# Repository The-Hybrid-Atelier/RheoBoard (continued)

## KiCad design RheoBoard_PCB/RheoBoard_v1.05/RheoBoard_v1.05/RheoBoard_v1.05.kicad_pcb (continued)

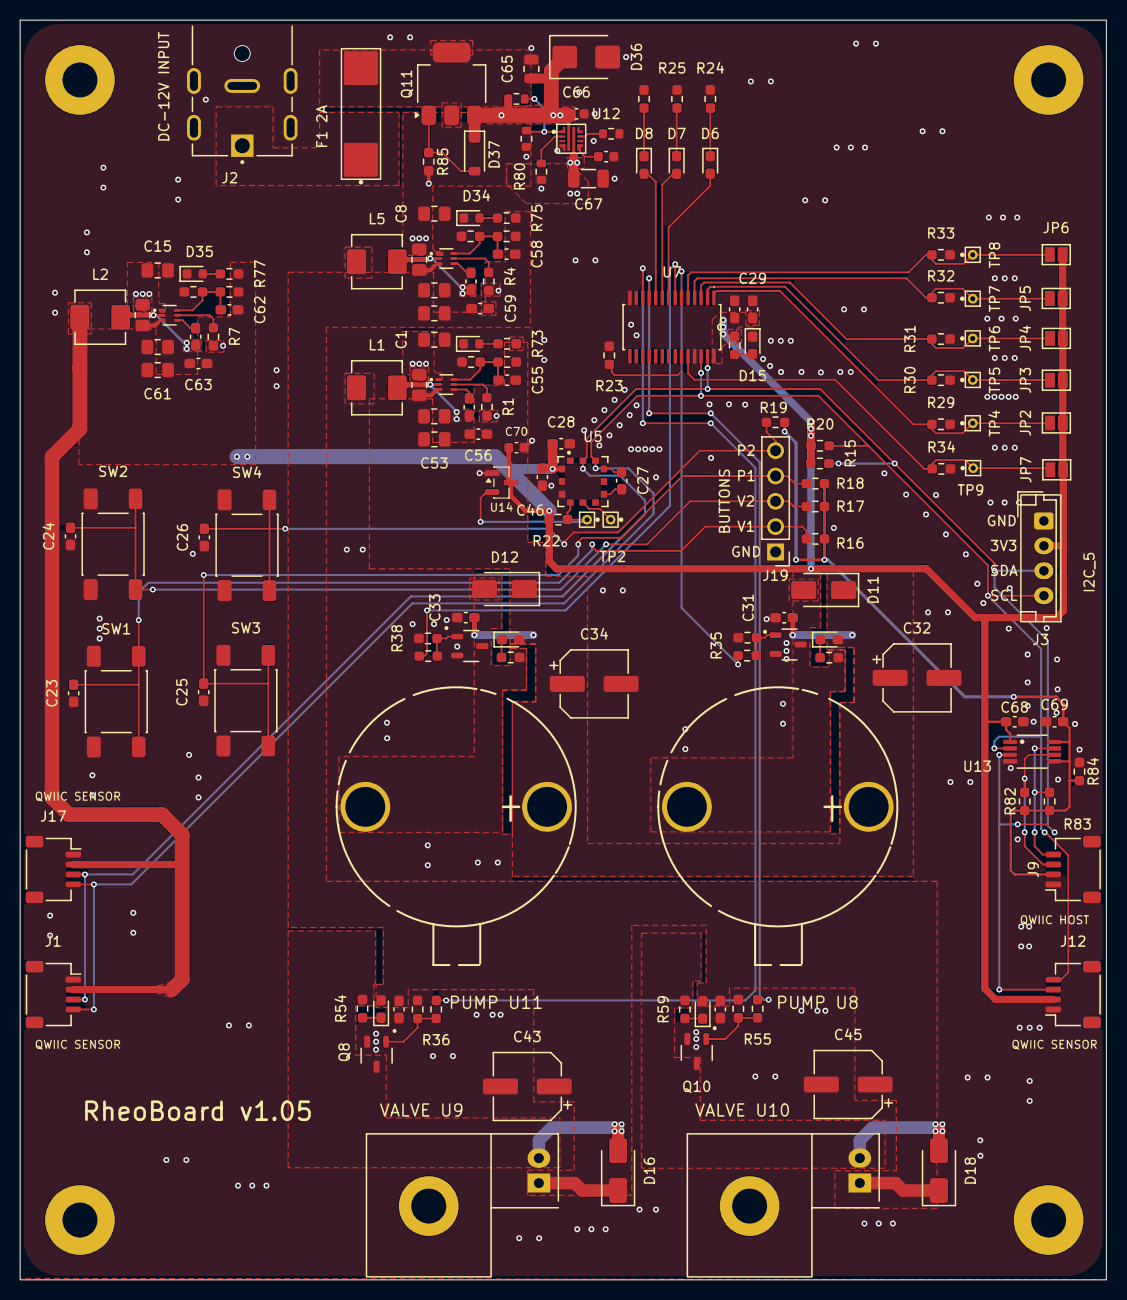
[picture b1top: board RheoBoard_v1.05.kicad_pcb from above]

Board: 2 copper layers, 109.0 x 126.4 mm, 162 parts (0 on the bottom side), 71 nets.

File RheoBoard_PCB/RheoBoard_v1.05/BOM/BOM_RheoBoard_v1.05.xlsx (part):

Comment | Designator | Footprint | LCSC / JLCPCB part | Qty | Unit USD (5-board order) | Fitted parts / board USD | Selected part source | Datasheet / specification | Manufacturer part number | Manufacturer | Assembly | Revision notes | Maximum allowed tolerance | Substitution requirements | JLCPCB category | Available order quantity
10uF 25V X5R ±10% | C1, C2, C8, C9, C15, C16 | Capacitor_SMD:C_0805_2012Metric_Pad1.18x1.45mm_HandSolder | C5448891 | 6 | 0.0379 | 0.22740000000000002 | https://jlcpcb.com/partdetail/component/C5448891 |  | TCC0805X5R106K250FT | CCTC | SMT |  | 0.1 | Same capacitance, footprint, voltage and dielectric. Preserve effective capacit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 | Extended | 149131
100nF 50V X7R ±10% | C3, C4, C5, C23, C24, C25, C26, C30, C31, C33, C42, C44, C46, C56, C59, C63, C6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 | Capacitor_SMD:C_0603_1608Metric_Pad1.08x0.95mm_HandSolder | C14663 | 18 | 0.0081 | 0.14579999999999999 | https://jlcpcb.com/partdetail/component/C14663 |  | CC0603KRX7R9BB104 | YAGEO | SMT | C68/C69 added as local/host U13 supply bypass. | 0.1 | Same capacitance, footprint, voltage and dielectric. Preserve effective capacit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 | Basic | 30393077
1nF 50V X7R ±5% | C27 | Capacitor_SMD:C_0603_1608Metric_Pad1.08x0.95mm_HandSolder | C5360811 | 1 | 0.0050999999999999995 | 0.0050999999999999995 | https://jlcpcb.com/partdetail/component/C5360811 |  | TCC0603X7R102J500CT | CCTC | SMT |  | 0.05 | Same capacitance, footprint, voltage and dielectric. Preserve effective capacit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 | Extended | 71799
10uF 25V X5R ±10% | C28, C29 | Capacitor_SMD:C_0603_1608Metric_Pad1.08x0.95mm_HandSolder | C7393892 | 2 | 0.0356 | 0.0712 | https://jlcpcb.com/partdetail/component/C7393892 |  | TCC0603X5R106K250CT | CCTC | SMT |  | 0.1 | Same capacitance, footprint, voltage and dielectric. Preserve effective capacit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 | Extended | 402730
22uF 50V ±20% | C32, C34, C43, C45 | Capacitor_SMD:CP_Elec_6.3x5.8 | C128458 | 4 | 0.179 | 0.716 | https://jlcpcb.com/partdetail/component/C128458 | https://industrial.panasonic.com/cdbs/www-data/pdf/RDE0000/A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 | EEEFK1H220P | Panasonic | SMT | Reduced from 100uF to 22uF; each pump/valve rail is approximately 88.3uF nomina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 | 0.2 | Same capacitance, footprint, voltage and dielectric. Preserve effective capacit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 | Extended | 5494
22uF 25V X5R ±20% | C52, C53, C54, C57, C60, C61 | Capacitor_SMD:C_0805_2012Metric_Pad1.18x1.45mm_HandSolder | C20416420 | 6 | 0.1334 | 0.8004 | https://jlcpcb.com/partdetail/component/C20416420 |  | TCC0805X5R226M250FT | CCTC | SMT |  | 0.2 | Same capacitance, footprint, voltage and dielectric. Preserve effective capacit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 | Extended | 87761
18pF 50V C0G ±5% | C55 | Capacitor_SMD:C_0603_1608Metric_Pad1.08x0.95mm_HandSolder | C107040 | 1 | 0.0067 | 0.0067 | https://jlcpcb.com/partdetail/component/C107040 |  | CC0603JRNPO9BN180 | YAGEO | SMT | 18 pF C0G 5%; same nominal value. | 0.05 | 5% or better, 18 pF C0G/NP0, >=50 V, 0603. Do not use X7R/X5R here. | Extended | 697605
24pF 50V C0G ±5% | C62 | Capacitor_SMD:C_0603_1608Metric_Pad1.08x0.95mm_HandSolder | C107044 | 1 | 0.0109 | 0.0109 | https://jlcpcb.com/partdetail/component/C107044 |  | CC0603JRNPO9BN240 | YAGEO | SMT | 24 pF C0G 5%; scales feed-forward timing for R61 100k. Bench transient check re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 | 0.05 | 5% or better, 24 pF C0G/NP0, >=50 V, 0603. | Extended | 23936
3.3nF 50V X7R ±10% | C64 | Capacitor_SMD:C_0603_1608Metric | C107088 | 1 | 0.0055 | 0.0055 | https://jlcpcb.com/partdetail/component/C107088 |  | CC0603KRX7R9BB332 | YAGEO | SMT | New controlled-startup timing capacitor for U12. | 0.1 | Same capacitance, footprint, voltage and dielectric. Preserve effective capacit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 | Extended | 506819
1uF 50V X7R ±10% | C65 | Capacitor_SMD:C_0805_2012Metric | C91185 | 1 | 0.0348 | 0.0348 | https://jlcpcb.com/partdetail/component/C91185 | https://www.yageogroup.com/download/specsheet/CC0805KKX7R9BB105 | CC0805KKX7R9BB105 | YAGEO | SMT | New local input bypass for U12; place beside IN/GND. | 0.1 | Same capacitance, footprint, voltage and dielectric. Preserve effective capacit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 | Extended | 317889
100nF 50V X7R ±10% | C66, C70 | Capacitor_SMD:C_0603_1608Metric | C14663 | 2 | 0.0081 | 0.0162 | https://jlcpcb.com/partdetail/component/C14663 |  | CC0603KRX7R9BB104 | YAGEO | SMT | Local high-frequency bypass for U12 and U14. | 0.1 | Same capacitance, footprint, voltage and dielectric. Preserve effective capacit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 | Basic | 30393077
4.7uF 50V X7R ±10% | C67 | Capacitor_SMD:C_1206_3216Metric | C132170 | 1 | 0.1189 | 0.1189 | https://jlcpcb.com/partdetail/component/C132170 | https://www.yageogroup.com/download/specsheet/CC1206KKX7R9BB475 | CC1206KKX7R9BB475 | YAGEO | SMT | New local output bypass for U12; place beside OUT/GND. | 0.1 | Same capacitance, footprint, voltage and dielectric. Preserve effective capacit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 | Extended | 16653
DMP6023LE-13 | Q11 | RheoBoard:SOT-223-3_TabPin2_DFM | C154901 | 1 | 0.624 | 0.624 | https://jlcpcb.com/partdetail/component/C154901 | https://www.diodes.com/datasheet/download/DMP6023LE.pdf | DMP6023LE-13 | Diodes Incorporated | SMT | Replaces D1 with lower-loss reverse-polarity protection. 1 gate, 2 drain/tab to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 |  |  | Extended | 476
LED_Red | D6, D7, D8, D13, D14, D15, D17, D19 | RheoBoard:LED_SZYY0603R_A1_K2_HandSolder | C434419 | 8 | 0.0137 | 0.1096 | https://jlcpcb.com/partdetail/component/C434419 | https://datasheet.lcsc.com/datasheet/pdf/7948f9a4498910c84f6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 | SZYY0603R | Yongyu Photoelectric | SMT | Manufacturer numbering: 1=A(+), 2=K(-). Cathode bar marks pad 2. See LED assemb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 |  |  | Extended | 830337
SS34 | D11, D12, D16, D18 | Diode_SMD:D_SMA | C115205 | 4 | 0.037700000000000004 | 0.15080000000000002 | https://jlcpcb.com/partdetail/component/C115205 |  | SS34 | Jingdao Microelectronics | SMT | SMA footprint and polarity mark match selected Jingdao SS34. |  |  | Extended | 61565
LED_Red | D33, D34, D35 | RheoBoard:LED_SZYY0603R_A1_K2_Nominal | C434419 | 3 | 0.0137 | 0.0411 | https://jlcpcb.com/partdetail/component/C434419 | https://datasheet.lcsc.com/datasheet/pdf/7948f9a4498910c84f6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 | SZYY0603R | Yongyu Photoelectric | SMT | Manufacturer numbering: 1=A(+), 2=K(-). Cathode bar marks pad 2. See LED assemb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 |  |  | Extended | 830337
SMBJ13A | D36 | Diode_SMD:D_SMB | C151252 | 1 | 0.14250000000000002 | 0.14250000000000002 | https://jlcpcb.com/partdetail/component/C151252 | https://www.littelfuse.com/assetdocs/tvs-diodes-smbj-series-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 | SMBJ13A | Littelfuse | SMT | Exact Littelfuse SMBJ13A. 13 V standoff, 21.5 V clamp at 28 A. Marking LG; cath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 |  |  | Extended | 1226
2A time-delay JFC1032-1200TS | F1 | RheoBoard:Fuse_JDT_JFC1032TS_10.25x3.2mm | C53035082 | 1 | 0.2938 | 0.2938 | https://jlcpcb.com/partdetail/component/C53035082 | https://www.jdtfuse.com/upload/PDF/JFC1032TS.pdf | JFC1032-1200TS | JDTfuse | SMT | Corrected centered origin and JDT land pattern. Check the new placement preview. |  |  | Extended | 1504
JST SH 4-pin 1.00mm | J1, J9, J12, J17 | Connector_JST:JST_SH_SM04B-SRSS-TB_1x04-1MP_P1.00mm_Horizontal | C160404 | 4 | 0.2149 | 0.8596 | https://jlcpcb.com/partdetail/component/C160404 | https://www.jst-mfg.com/product/pdf/eng/eSH.pdf | SM04B-SRSS-TB(LF)(SN) | JST | SMT | Standard Qwiic pin order: 1 GND, 2 3.3 V, 3 SDA, 4 SCL. J9 is the dedicated MAS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 |  |  | Extended | 65620
PJ-082BH | J2 | RheoBoard:PJ-082BH | C3094233 | 1 | 2.608 | 2.608 | https://www.lcsc.com/product-detail/C3094233.html | https://www.sameskydevices.com/product/resource/pj-082bh.pdf | PJ-082BH | CUI | Manual THT | Manual through-hole assembly. Center-positive 12 V, 5.5 x 2.5 mm mating plug.
JST EH 4-pin 2.50mm | J3 | RheoBoard:JST_EH_B4B-EH-A_1x04_P2.50mm_Vertical_DFM | C160258 | 1 | 0.0613 | 0.0613 | https://www.lcsc.com/product-detail/C160258.html | https://www.jst-mfg.com/product/pdf/eng/eEH.pdf | B4B-EH-A(LF)(SN) | JST | Manual THT | Manual through-hole assembly. Pin 2 supplies local 3.3 V to peripherals.
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
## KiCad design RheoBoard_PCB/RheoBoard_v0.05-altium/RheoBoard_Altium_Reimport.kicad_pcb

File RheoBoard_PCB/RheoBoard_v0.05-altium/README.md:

# RheoBoard v0.05 Altium conversion

Open `RheoBoard_Altium_Reimport.kicad_pro` in KiCad 10. This historical conversion is separate from the later native v1 and v1.05 designs. The original Altium archive is retained in `RheoBoard_v0.05.rar`.

The import recovered MAIN, POWER and a drawing-only block-diagram sheet, plus a two-layer PCB and its imported footprint library. Eight external illustrations were unavailable. The flat schematic sheets require connectivity and reference reconciliation before schematic-to-board updates.

This conversion is not ready for fabrication. The retained design includes a backside copper overlap between pump 1 and a valve switched node, an unconnected controller LED5 output and missing valve-2 controller drive, plus ERC/DRC findings involving clearances, copper edges, annular rings, mask and imported library links. No fabrication package was regenerated for this conversion. Use the later revision folders for their corresponding designs; do not mix their outputs.

Hardware design licensing follows the repository root LICENSE, CERN-OHL-W-2.0. Documentation is CC BY-SA 4.0.

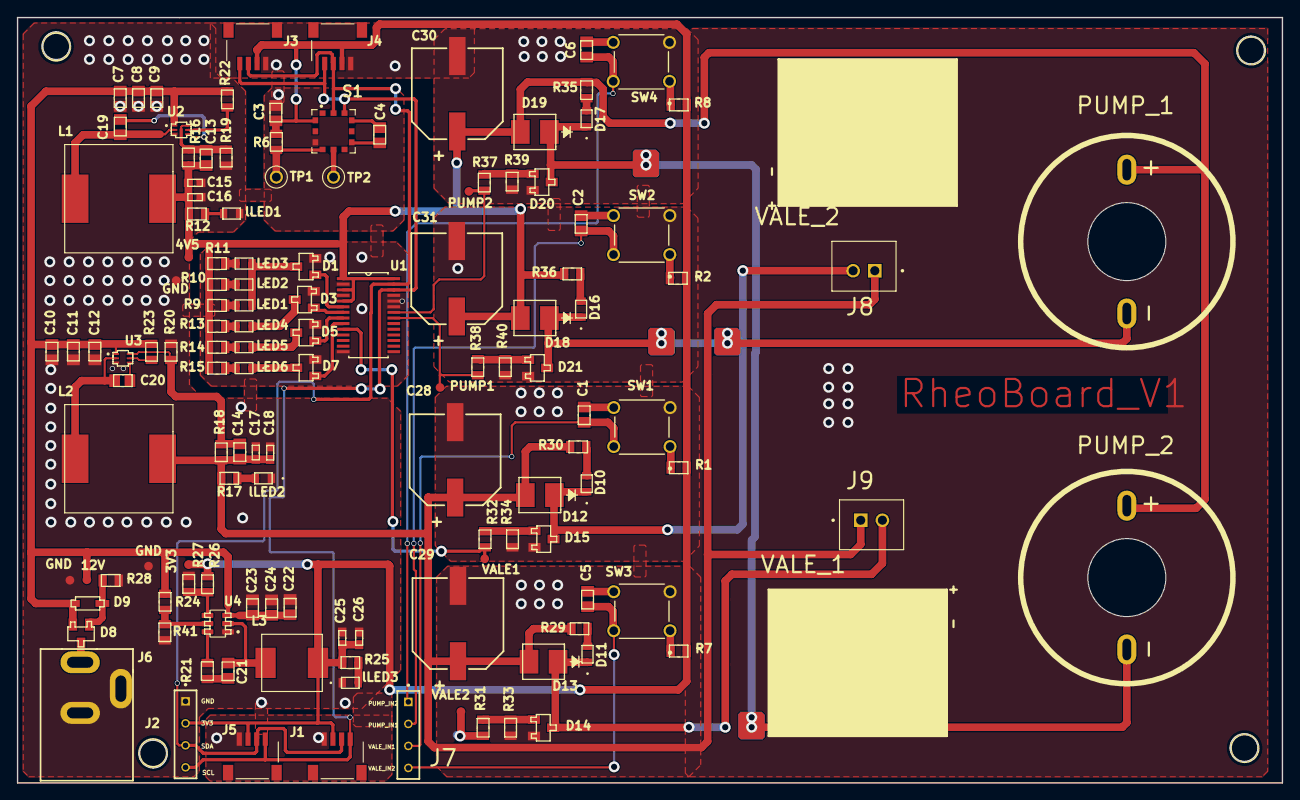
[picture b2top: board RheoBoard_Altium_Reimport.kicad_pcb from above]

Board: 2 copper layers, 146.0 x 88.3 mm, 132 parts (0 on the bottom side), 71 nets.

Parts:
3V3, 4V5, 12V: TP_1MM; TP_1mm
C1, C2, C3, C5, C6, C9, C12, C19, C20, C21, C22: 0.1UF,50V; CAP_CER_0805
C4: 1nF 50V; CAP_CER_0805
C7, C8, C10, C11: 10UF 50V; CAP_CER_0805
C13, C14: 18pF 50V; CAP_CER_0805
C15, C16, C17, C18, C25, C26: 22uF 6.3V; CAP_CER_0603
C23, C24: 10UF 25V; CAP_CER_0805
C28, C29, C30, C31: 100uF 25V; CAP_ALUM_SMD_D10_H12.4
D1, D3, D5, D7, D14, D15, D20, D21: 30V 5.8A; SOT-23-3
D8: 20V 4A; SOT-23-3
D9: BZT52C5V1; SOD-123
D10, D11, D16, D17: Led green; LED_LS R976_AOS
D12, D13, D18, D19: 3A 40V; DO214AA
GND: TP_1MM; TP_1mm
GND#2, GND#3: TP_1MM; TP_1mm
J1, J3, J4, J5: 14417; SPARKFUN_PRT-14417
J2: TS-104-T-A; HDR_THT_1X04_P2.54
J6: 694106301002; CONN PWR JACK 2.1X5.5MM SOLDER
J7: TS-104-T-A; HDR_THT_1x04_P2.54
J8, J9: VERT; CONN_SMD_TOP_P2.50
L1, L2: 2.2uH; IND_12.5x12.5_H8.5
L3: 4.7uH; IND_6.8X6.5_H2.8
LED1, LED2, LED3: RED 2V 20mA; LED_LS R976_AOS
LED4, LED5, LED6: Led green; LED_LS R976_AOS
PUMP1, PUMP2: TP_1MM; TP_1mm
PUMP_1, PUMP_2: 0010844022; PUMP_LPM - ZR370-02PM
R1, R2, R6, R7, R8, R33, R34, R39, R40: 10K 1% 0805; RES_0805
R9, R10, R11, R13, R14, R15, R29, R30, R35, R36: 220R 0805; RES_0805
R12, R17: 1K 1% 0805; RES_0805
R16: 130K 0805; RES_0805
R18: 270K 0805; RES_0805
R19: 20K 0805; RES_0805
R20: 30K 0805; RES_0805
R21: 30Ohm 0805; RES_0805
R22, R23, R28: 100K 0805; RES_0805
R24: 174K 0805; RES_0805
R25: 470R 0805; RES_0805
R26: 75K 0805; RES_0805
R27: 24K 0805; RES_0805
R31, R32, R37, R38: 100R 0805; RES_0805
R41: 36.5K 0805; RES_0805
S1: MPRLS0025PA00001A; XDCR_MPRLS0025PA00001A
SW1, SW2, SW3, SW4: B3F-1020; SW_B3F-1000_OMR
TP1, TP2: 5002; KEYSTONE_5002
U1: PCA9685PW,118; TSSOP-28
U2, U3: TPS563203DRLR; SOT-563
U4: TPS56339DDCT; SOT-23-6
VALE1, VALE2: TP_1MM; TP_1mm
VALE_1, VALE_2: 0010844022; VALE_FA0520E
lLED1, lLED2, lLED3: RED 2V 20mA; LED_LS R976_AOS

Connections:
+12: 12V.1, C7.2, C8.2, C9.2, C10.2, C11.2, C12.2, C22.2, C23.2, C24.2, D8.2, D9.1, R22.2, R23.2, R24.2, U2.1, U3.1, U4.3
GND: C3.2, C7.1, C8.1, C9.1, C10.1, C11.1, C12.1, C15.1, C16.1, C17.1, C18.1, C22.1, C23.1, C24.1, C25.1, C26.1, C28.2, C29.2, C30.2, C31.2, D1.2, D3.2, D5.2, D7.2, D14.2, D15.2, D20.2, D21.2, GND.1, GND#2.1, GND#3.1, J1.1, J2.01, J3.1, J4.1, J5.1, J6.2, J6.3, R19.2, R20.1, R27.1, R28.1, R33.1, R34.1, R39.1, R40.1, R41.1, S1.10, SW1.3, SW2.3, SW3.3, SW4.3, U1.2, U1.4, U1.14, U1.23, U1.24, U1.25, U2.3, U3.3, U4.1, lLED1.1, lLED2.1, lLED3.1
Net3V3_1: 3V3.1, C3.1, C25.2, C26.2, J1.2, J2.02, J3.2, J4.2, J5.2, L3.2, R1.2, R2.2, R6.2, R7.2, R8.2, R25.2, R26.2, S1.12
Net4V5_1: 4V5.1, C13.2, C15.2, C16.2, C30.1, C31.1, D18.2, D19.2, L1.1, PUMP_1.1, PUMP_2.1, R9.2, R10.2, R11.2, R12.2, R13.1, R14.1, R15.1, R16.2, R35.1, R36.1, U1.1, U1.3, U1.5, U1.28
NetC1_1: C1.1, SW1.4
NetC2_1: C2.1, SW2.4
NetC4_1: C4.1, S1.6
NetC4_2: C4.2, S1.4
NetC5_1: C5.1, SW3.4
NetC6_1: C6.1, SW4.4
NetC13_1: C13.1, R16.1, R19.1, U2.6
NetC14_1: C14.1, R18.1, R20.2, U3.6
NetC14_2: C14.2, C17.2, C18.2, C28.1, C29.1, D12.2, D13.2, J8.1, J9.1, L2.1, R17.2, R18.2, R29.1, R30.1
NetC19_1: C19.1, L1.2, U2.2
NetC19_2: C19.2, U2.4
NetC20_1: C20.1, L2.2, U3.2
NetC20_2: C20.2, U3.4
NetC21_1: C21.1, L3.1, U4.2
NetC21_2: C21.2, R21.2
NetD1_1: D1.1, U1.6
NetD1_3: D1.3, LED1.1, LED2.1, LED3.1
NetD3_1: D3.1, U1.7
NetD3_3: D3.3, LED4.1
NetD5_1: D5.1, U1.8
NetD5_3: D5.3, LED5.1
NetD7_1: D7.1, U1.9
NetD7_3: D7.3, LED6.1
NetD8_1: D8.1, D9.2, R28.2
NetD8_3: D8.3, J6.1
NetD10_1: D10.1, D12.1, D15.3, J8.2
NetD10_2: D10.2, R30.2
NetD11_1: D11.1, D13.1, D14.3, J9.2
NetD11_2: D11.2, R29.2
NetD14_1: D14.1, R31.2, R33.2
NetD15_1: D15.1, R32.2, R34.2
NetD16_1: D16.1, D18.1, D21.3, PUMP_1.2
NetD16_2: D16.2, R36.2
NetD17_1: D17.1, D19.1, D20.3, PUMP_2.2
NetD17_2: D17.2, R35.2
NetD20_1: D20.1, R37.2, R39.2
NetD21_1: D21.1, R38.2, R40.2
NetLED1_2: LED1.2, R9.1
NetLED2_2: LED2.2, R10.1
NetLED3_2: LED3.2, R11.1
NetLED4_2: LED4.2, R13.2
NetLED5_2: LED5.2, R14.2
NetLED6_2: LED6.2, R15.2
NetPUMP1_1: PUMP1.1, R38.1, U1.21
NetPUMP2_1: PUMP2.1, R37.1, U1.22
NetR1_1: R1.1, SW1.1
NetR2_1: R2.1, SW2.1
NetR6_1: R6.1, S1.9, TP1.TP
NetR7_1: R7.1, SW3.1
NetR8_1: R8.1, SW4.1
NetR21_1: R21.1, U4.6
NetR22_1: R22.1, U2.5
NetR23_1: R23.1, U3.5
NetR24_1: R24.1, R41.2, U4.5
NetR26_1: R26.1, R27.2, U4.4
NetR31_1: R31.1, VALE2.1
NetR32_1: R32.1, U1.10, VALE1.1
NetS1_8: S1.8, TP2.TP
NetlLED1_2: R12.1, lLED1.2
NetlLED2_2: R17.1, lLED2.2
NetlLED3_2: R25.1, lLED3.2
PUMP1_IN: C2.2, J7.02, SW2.2
PUMP2_IN: C6.2, J7.01, SW4.2
SCL: J1.4, J2.04, J3.4, J4.4, J5.4, S1.3, U1.26
SDA: J1.3, J2.03, J3.3, J4.3, J5.3, S1.2, U1.27
VALE1_IN: C1.2, J7.03, SW1.2
VALE2_IN: C5.2, J7.04, SW3.2

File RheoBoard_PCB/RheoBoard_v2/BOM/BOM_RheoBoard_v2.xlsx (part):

RheoBoard v2 purchasing BOM
Quantities are for one board. Parts cost controls the batch size and shows whic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
Enter USD quotes in column F. Filter v1.05 reuse for shared parts. Check select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
Component | Designators | Altium footprint | Supplier SKU | Qty / board | Unit USD | Parts / board USD | Purchase source | Datasheet / spec | Sourcing MPN / model | Manufacturer | Assembly | Selection | Design MPN / model | Purchasing note | Min. order | Order multiple | Price from qty | Qty needed | Order qty | Order USD | Supplier | LCSC / JLCPCB ID | Catalog relationship | Price basis | Price through qty | Tolerance | v1.05 reuse | v1.05 source | Alternate source
16-channel PWM controller | U1 | TSSOP-28 | C2678753 | 1 |  |  | Supplier listing | Specification | PCA9685PW,118 | NXP Semiconductors | SMT | Selected | PCA9685PW,118 |  | 1 | 1 | 1 | 5 | 5 |  | LCSC | C2678753 | Design MPN | Enter supplier quote |  |  | Same MPN · C2678753 | v1.05 supplier
25 psi absolute I²C pressure sensor | S1 | XDCR_MPRLS0025PA00001A | C3257154 | 1 |  |  | Supplier listing | Specification | MPRLS0025PA00001A | Honeywell | SMT | Selected | MPRLS0025PA00001A |  | 1 | 1 | 1 | 5 | 5 |  | LCSC | C3257154 | Design MPN | Enter supplier quote |  |  | Same MPN · C3257154 | v1.05 supplier
3 A step-down regulator (4.5 V and 6 V rails) | U2, U3 | SOT-563 | 296-TPS563203DRLRCT-ND | 2 |  |  | Supplier listing | Specification | TPS563203DRLR | Texas Instruments | SMT | Selected | TPS563203DRLR |  | 1 | 1 | 1 | 10 | 10 |  | DigiKey | C22445512 | Design MPN | Enter supplier quote |  |  | Same MPN · C22445512 | v1.05 supplier
3 A step-down regulator (3.3 V rail) | U4 | SOT-23-6 | 296-53564-1-ND | 1 |  |  | Supplier listing | Specification | TPS56339DDCT | Texas Instruments | SMT | Selected | TPS56339DDCT |  | 1 | 1 | 1 | 5 | 5 |  | DigiKey | C2071585 | Design MPN | Enter supplier quote
2.2 µH shielded power inductor | L1, L2 | IND_12.5x12.5_H8.5 | 3502182 | 2 |  |  | Candidate source | Specification | B82477G4222M000 | TDK | SMT | Review | IFSC1515AHER2R2M01 | The 4 mm schematic part cannot span the 7 mm copper gap. TDK matches the lands.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 | 1 | 1 | 1 | 10 |  |  | DigiKey |  |  | Enter supplier quote |  | 20% |  |  | Design MPN only
4.7 µH power inductor | L3 | IND_6.8X6.5_H2.8 | 308-2466-1-ND | 1 |  |  | Supplier listing | Specification | 0630CDMCCDS-4R7MC | Sumida | SMT | Selected | 0630CDMCCDS-4R7MC |  | 1 | 1 | 1 | 5 | 5 |  | DigiKey | C167294 | Design MPN | Enter supplier quote |  | 20%
P-channel MOSFET | D8 | SOT-23-3 | C96616 | 1 |  |  | Supplier listing |  | DMG3415U-7 | Diodes Inc. | SMT | Selected | DMG3415U-7 |  | 5 | 5 | 1 | 5 | 5 |  | LCSC | C96616 | Design MPN | Enter supplier quote
5.1 V Zener diode | D9 | SOD-123 | BZT52C5V1-FDICT-ND | 1 |  |  | Supplier listing |  | BZT52C5V1-7-F | Diodes Inc. | SMT | Selected | BZT52C5V1-7-F |  | 1 | 1 | 1 | 5 | 5 |  | DigiKey | C151588 | Design MPN | Enter supplier quote |  | 6%
N-channel MOSFET | D1, D3, D5, D7, D14, D15, D20, D21 | SOT-23-3 | C20917 | 8 |  |  | Supplier listing |  | AO3400A | Alpha & Omega | SMT | Selected | AO3400A |  | 5 | 5 | 1 | 40 | 40 |  | LCSC | C20917 | Design MPN | Enter supplier quote |  |  | Same MPN · C20917 | v1.05 supplier
3 A, 40 V Schottky flyback diode | D12, D13, D18, D19 | DO214AA | C85099 | 4 |  |  | Candidate source | Specification | B340B-13-F | Diodes Incorporated | SMT | Review | SS34 | The onsemi SMC body exceeds the SMB footprint. Confirm the SMB candidate’s sold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 | 1 | 1 | 1 | 20 |  |  | JLCPCB |  |  | Enter supplier quote |  |  |  |  | Design MPN only
Red indicator LED, 0805 | LED1, LED2, LED3, lLED1, lLED2, lLED3 | LED_LS R976_AOS | 475-LSR976-NR-1CT-ND | 6 |  |  | Supplier listing |  | LS R976-NR-1-0-20-R18 | ams OSRAM | SMT | Selected | LS R976-NR-1-0-20-R18 |  | 1 | 1 | 1 | 30 | 30 |  | DigiKey | C2899997 | Design MPN | Enter supplier quote
Green indicator LED, 0805 lands | D10, D11, D16, D17, LED4, LED5, LED6 | LED_LS R976_AOS | C5456999 | 7 |  |  | Candidate source | Specification | LG R971-KN-1 | ams OSRAM | SMT | Review | LTST-C190GKT | Lite-On is 0603 on 0805 lands. Verify the OSRAM candidate’s polarity, pad overl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 | 1 | 1 | 1 | 35 |  |  | JLCPCB |  |  | Enter supplier quote |  |  |  |  | Design MPN only
4-pin Qwiic connector | J1, J3, J4, J5 | SPARKFUN_PRT-14417 | 1568-14417-ND | 4 |  |  | Supplier listing |  | 14417 | SparkFun | SMT | Selected | 14417 |  | 1 | 1 | 1 | 20 | 20 |  | DigiKey | C2859067 | Design MPN | Enter supplier quote |  |  | JST housing-color variant · C160404 | v1.05 supplier
4-position vertical pin header, 2.54 mm | J2, J7 | HDR_THT_1X04_P2.54 | 612-TS-104-T-A-ND | 2 |  |  | Supplier listing | Specification | TS-104-T-A | Samtec | Through-hole | Selected | TS-104-T-A | Use the Samtec -A lead option. Its recommended hole is 0.635 mm, matching the v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 | 1 | 1 | 1 | 10 | 10 |  | DigiKey | C6886151 | Design MPN | Enter supplier quote
DC jack, 2.1 × 5.5 mm | J6 | CONN PWR JACK 2.1X5.5MM SOLDER | 732-5930-ND | 1 |  |  | Supplier listing | Specification | 694106301002 | Würth Elektronik | Through-hole | Selected | 694106301002 |  | 1 | 1 | 1 | 5 | 5 |  | DigiKey |  |  | Enter supplier quote
2-position XH valve header, 2.50 mm | J8, J9 | CONN_SMD_TOP_P2.50 | C158012 | 2 |  |  | Supplier listing | Specification | B2B-XH-A(LF)(SN) | JST | Through-hole | Selected | B2B-XH-A |  | 20 | 20 | 1 | 10 | 20 |  | LCSC | C158012 | XH family, check plated suffix | Enter supplier quote |  |  | Matching XH header · C158012 | v1.05 supplier
Momentary tactile switch | SW1, SW2, SW3, SW4 | SW_B3F-1000_OMR | SW402-ND | 4 |  |  | Supplier listing |  | B3F-1020 | Omron | Through-hole | Selected | B3F-1020 |  | 1 | 1 | 1 | 20 | 20 |  | DigiKey | C722171 | Design MPN | Enter supplier quote
White miniature test point | TP1, TP2 | KEYSTONE_5002 | C238123 | 2 |  |  | Supplier listing |  | 5002 | Keystone | Through-hole | Selected | 5002 |  | 5 | 5 | 1 | 10 | 10 |  | LCSC | C238123 | Design MPN | Enter supplier quote
100 nF, 50 V, 0805 | C1, C2, C3, C5, C6, C9, C12, C19, C20, C21, C22 | CAP_CER_0805 | 0805B104J500BD | 11 |  |  | Candidate source | Specification | 0805B104J500BD | NextGen Component | SMT | Review | 0805B104K500BD | Schematic symbol specifies ±5%. Its named K-grade part is ±10%. The J-grade alt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 | 1 | 1 | 1 | 55 |  |  | NextGen Component |  |  | Enter supplier quote |  |  |  |  | Design MPN (±10%)
1 nF, 50 V, 0805 | C4 | CAP_CER_0805 | 399-C0805C102K5HACAUTOCT-ND | 1 |  |  | Supplier listing |  | C0805C102K5HACAUTO | Yageo Group | SMT | Selected | C0805C102K5HACAUTO |  | 1 | 1 | 1 | 5 | 5 |  | DigiKey | C1513171 | Design MPN | Enter supplier quote
10 µF, 50 V, 0805 | C7, C8, C10, C11 | CAP_CER_0805 | 3372-0805W106K500CCTR-ND | 4 |  |  | Supplier listing |  | 0805W106K500CC | Nextgen | SMT | Selected | 0805W106K500CC | The recorded NextGen/Aillen part is supplied in reels of 3,000. Samsung CL21A10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 | 3000 | 3000 | 1 | 20 | 3000 |  | DigiKey Marketplace |  |  | Enter supplier quote |  |  |  |  | Samsung candidate
18 pF, 50 V, 0805 | C13, C14 | CAP_CER_0805 | 49AM7940 | 2 |  |  | Supplier listing |  | C0805C180J5HACTU | Yageo Group | SMT | Selected | C0805C180J5HACTU |  | 10 | 1 | 1 | 10 | 10 |  | Newark |  |  | Enter supplier quote
22 µF, 6.3 V, 0603 | C15, C16, C25, C26 | CAP_CER_0603 | 490-10471-1-ND | 4 |  |  | Supplier listing | Specification | GRM188C80J226ME15D | Murata | SMT | Selected | GRM188C80J226ME15D |  | 1 | 1 | 1 | 20 | 20 |  | DigiKey | C393031 | Design MPN | Enter supplier quote |  | 20%
22 µF, 0603, for the 6 V rail | C17, C18 | CAP_CER_0603 | C2762594 | 2 |  |  | Candidate source | Specification | CL10A226MO7JZNC | Samsung Electro-Mechanics | SMT | Review | GRM188C80J226ME15D | The 6.3 V schematic part has little margin on the 6 V rail. The 16 V candidate 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 | 1 | 1 | 1 | 10 |  |  | JLCPCB |  |  | Enter supplier quote |  | 20% |  |  | Design MPN only
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
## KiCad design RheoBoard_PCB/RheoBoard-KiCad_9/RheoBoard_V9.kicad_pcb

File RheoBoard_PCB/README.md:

# RheoBoard PCB

## Current PCB — v2

The assembled and tested v2 board is marked `RheoBoard_V2`. Open the [v2 project in Altium Designer](RheoBoard_v2/Altium/RheoBoard_v2.PrjPcb).

[PCB layout](RheoBoard_v2/Altium/RheoBoard_v2.PcbDoc) · [Main schematic](RheoBoard_v2/Altium/MAIN.SchDoc) · [Power schematic](RheoBoard_v2/Altium/POWER.SchDoc) · [Parts library](RheoBoard_v2/Altium/RheoBoard_v2.IntLib) · [v2 file index](RheoBoard_v2/README.md)

[Complete v2 project ZIP](RheoBoard_v2/RheoBoard_v2-Altium.zip) · [Purchasing BOM (Excel)](RheoBoard_v2/BOM/BOM_RheoBoard_v2.xlsx) · [Gerbers, NC drills and board views](RheoBoard_v2/README.md#bare-board-artwork) · [STEP model and preview](RheoBoard_v2/README.md#3d-model)

For a bare-board order, use the [v2 JLCPCB upload ZIP and order settings](RheoBoard_v2/Manufacturing/JLCPCB/README.md).

## FA0520E valve holder

All RheoBoard PCB revisions and RheoBoardOTS DIY share this valve-holder design. Four low stops locate three sides of the metal valve frame and leave the plastic head open.

[SolidCraft 0.30.1 project](../mechanical/valve-holder/FA0520E-valve-holder.sc) · [STEP model](../mechanical/valve-holder/FA0520E-valve-holder.step) · [Printable STL](../mechanical/valve-holder/FA0520E-valve-holder.stl)

## Earlier revisions

- [v1.05](RheoBoard_v1.05/) — KiCad 10 project and manufacturing files.
- [Earlier Altium project](RheoBoard_v1-altium/RheoBoard_V1.PrjPcb) — v1 design snapshot.
- [v1](RheoBoard_v1/) — original KiCad project and outputs.
- [v0.05 Altium import](RheoBoard_v0.05-altium/) — historical imported design.

### v1.05 files

The v1.05 PCB uses a PCA9685 for pump and valve control, a nominal 5.4 V valve rail, J19 for host button inputs, and a reset supervisor for the MPRLS pressure sensor. The [RheoBoardOTS firmware](../code/firmware/README.md) targets the DIY controller. The v1.05 PCB requires its own actuator and button handling.

[Editable v1.05 diagram (SVG)](images/custom-pcb-block-diagram-v105.svg).

- [JLCPCB order folder](RheoBoard_v1.05/Manufacturing/JLCPCB/): matching fabrication ZIP, complete assembly BOM/CPL and ordering guide; 142 positions per board (137 surface-mount parts and five through-hole connectors), pumps U8/U11 excluded.
- [KiCad project](RheoBoard_v1.05/RheoBoard_v1.05/RheoBoard_v1.05.kicad_pro)
- [Schematic and board](RheoBoard_v1.05/RheoBoard_v1.05/)
- [Symbols](RheoBoard_v1.05/Symbol/), [footprints](RheoBoard_v1.05/Footprint/) and [3D models](RheoBoard_v1.05/3D/)
- [Full BOM workbook](RheoBoard_v1.05/BOM/BOM_RheoBoard_v1.05.xlsx) and [SMT-only BOM export](RheoBoard_v1.05/BOM/BOM_RheoBoard_v1.05_JLCPCB.csv)
- [Gerbers and drills](RheoBoard_v1.05/Manufacturing/Gerber/)
- [Fabrication ZIP](RheoBoard_v1.05/Manufacturing/RheoBoard_v1.05_fabrication.zip)
- [SMT-only placement CSV](RheoBoard_v1.05/Manufacturing/CPL/CPL_RheoBoard_v1.05_JLCPCB_SMT.csv) and [native position export](RheoBoard_v1.05/Manufacturing/CPL/RheoBoard_v1.05_native_positions.csv)
- [KiCad drawings](RheoBoard_v1.05/Manufacturing/Drawings/)

The external ESP32 controller, power supplies, valves, cables and tubing are separate purchases. See the [v1.05 wiki BOM](https://github.com/The-Hybrid-Atelier/RheoBoard/wiki/RheoBoard_v1.05-BOM) for the assembly scope and separate parts.

### System diagrams

The original v1 system overview shows the controller, sensor, pumps and valves.

Hardware license: CERN-OHL-W-2.0 — see [LICENSE](../LICENSE).

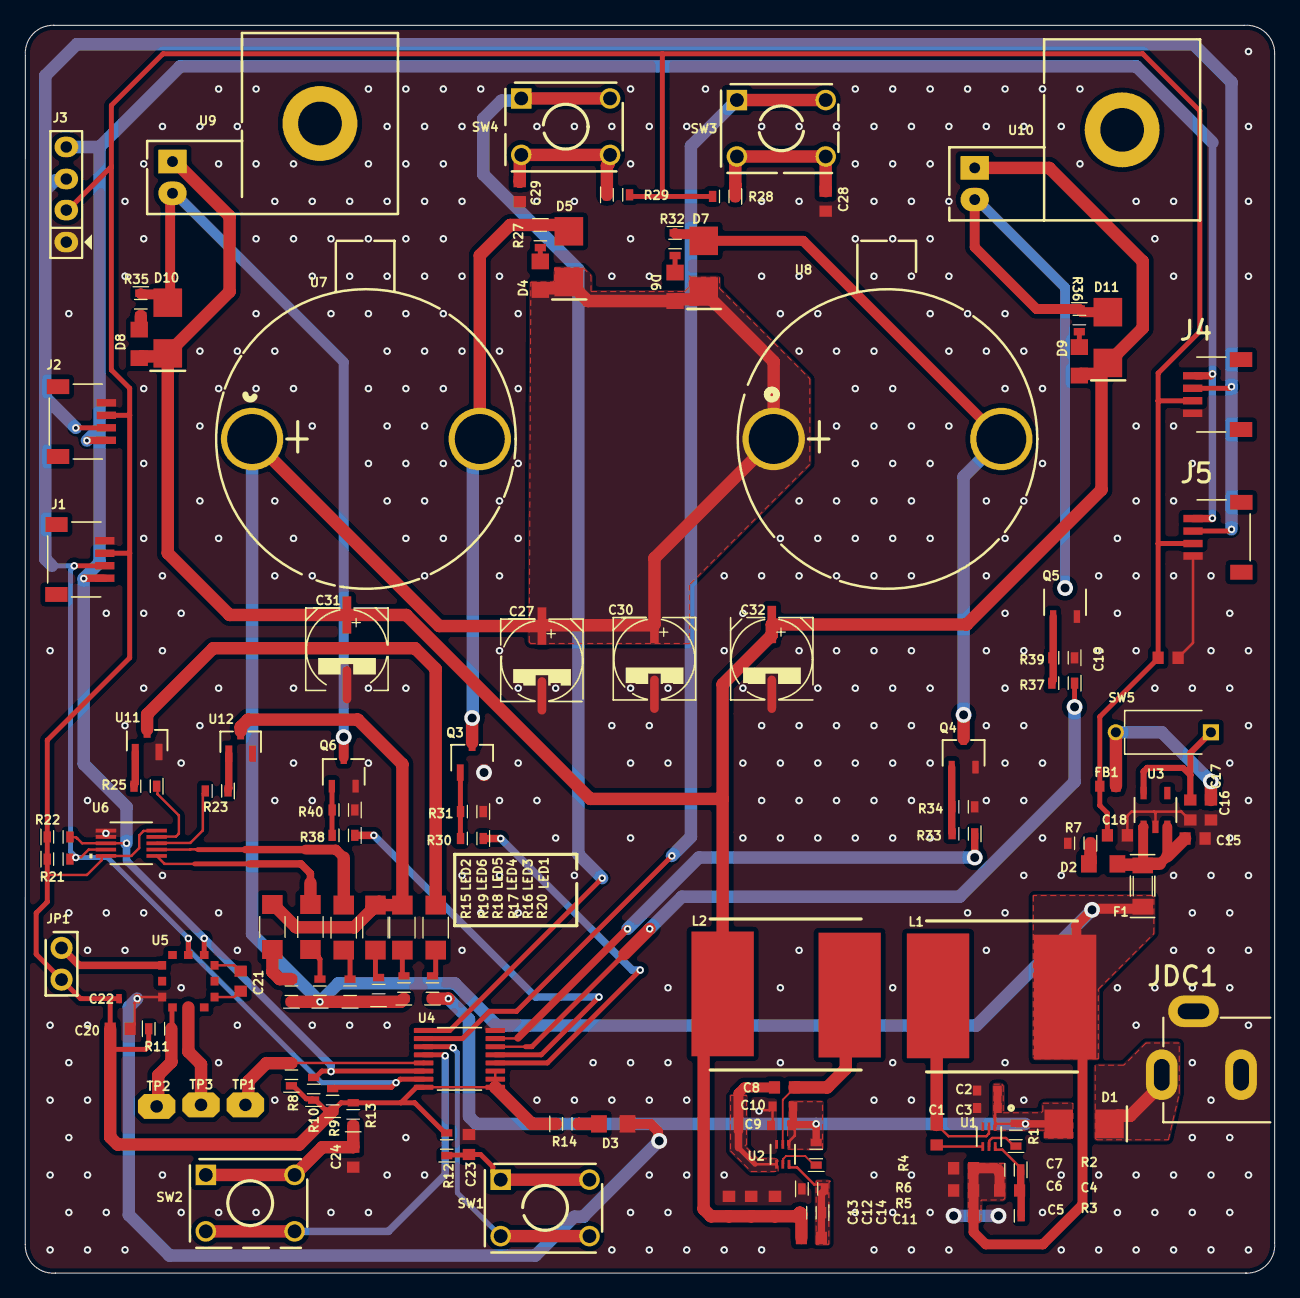
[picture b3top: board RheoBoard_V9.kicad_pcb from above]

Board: 2 copper layers, 100.1 x 100.0 mm, 120 parts (0 on the bottom side), 61 nets.

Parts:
C1, C4, C8, C11, C20, C23, C24, C28, C29: 100nF; CN-SMD-0603
C2, C3, C9, C10: 10uF; CAP_CL10_SAM
C5, C6, C7, C12, C13, C14: 22uF; CN-SMD-0603
C15, C17, C18: 10u; CN-SMD-0603
C16: 100n; CN-SMD-0603
C19: CAP ALUM 100UF 20% 16V SMD; CN-SMD-0603
C21: 1nF; CN-SMD-0603
C22: 100nF; CAP_CL10_SAM-L
C27, C30, C31, C32: CAP ALUM 100UF 20% 16V SMD; CAP-ALU-SMD-D
D1, D5, D7, D10, D11: SS34; DIO-SMD-106
D2, D3, D4, D6, D8, D9: LED Red; LED-0805-Red
F1: C1F5; RES-SMD-1206
FB1: 330; IND_BLM18KG331WH1D_MUR-L
J1, J2, J4, J5: PRT-14417; SPARKFUN_PRT-14417
J3: Jumper 4; JP4
JDC1: Jac DC 5521; DC0
JP1: JP2; JP2-CLOSED
L1, L2: 4.7uH; Inductor_SMD
LED1, LED2, LED3, LED4, LED5, LED6: LED; LED-1206-Red
Q3: AO3400A; SOT-23-3L_AOS
Q4, Q5, Q6: AO3400A; SOT-23-3L_AOS-L
R1, R4: RES 100K 5% 1/10W 0603; RES-SMD-0603
R2: 197K; RES-SMD-0603
R3: 30K; RES-SMD-0603
R5: 270K; RES-SMD-0603
R6: 30k; RES-SMD-0603
R7, R14, R20, R23, R25: 1K; RES-SMD-0603
R8: 2.2K; RES-SMD-0603
R9, R10: 4.7K; RES-SMD-0603
R11, R21, R22: 10K; RES-SMD-0603
R12, R13, R28, R29: 10k; RES-SMD-0603
R15, R16, R17, R18, R19: 220R; RES-SMD-0603
R27, R32, R35, R36: RES 1K 5% 1/10W 0603; RES-SMD-0603
R30, R33, R37, R38: RES 100R 5% 1/10W 0603; RES-SMD-0603
R31, R34, R39, R40: RES 10K 5% 1/10W 0603; RES-SMD-0603
SW1, SW2, SW3, SW4: SW2; BUTTON 4 PIN
SW5: SW; SW-DIP1
TP1, TP2, TP3: 1; TP - 2
U1, U2: TI TPS563203DRLR; SOT_07SDRLR_TEX
U3: AP2112K-3.3TRG1; SOT_RG1_DIO
U4: TCA9534APWR; SOP65P640X120-16N
U5: MPRLS0025PA00001A; XDCR_MPRLS0025PA00001A
U6: PCA9632DP2,118; TSSOP10_3P1X3P1_NXP
U7, U8: PUMP; Pump
U9: VALVE
U10: VALVE2; VALVE
U11, U12: BC817-40; SOT23_NEX

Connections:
3V3: C16.2, SW5.1, U3.5
4V5: C4.2, C5.2, C6.2, C7.2, C27.1, C30.1, D4.2, D5.1, D6.2, D7.1, F1.1, L1.2, R2.2, R15.1, R16.1, R17.1, R18.1, R19.1, U7.1, U8.1
4V5A: C15.2, D2.1, F1.2, U3.1, U3.3
6V: C11.2, C12.2, C13.2, C14.2, C31.1, C32.1, D8.2, D9.2, D10.1, D11.1, L2.2, R5.2, U9.1, U10.1
+12: D1.1, JDC1.1
D3V3: C18.2, C19.1, C20.2, C22.2, FB1.2, J1.2, J2.2, J3.2, J4.2, J5.2, JP1.2, R8.1, R9.1, R10.1, R11.1, R12.2, R13.2, R14.1, R21.1, R22.1, R28.2, R29.2, U4.1, U4.2, U4.3, U4.16, U6.5, U6.10
GND: C2.1, C3.1, C5.1, C6.1, C7.1, C9.1, C10.1, C12.1, C13.1, C14.1, C15.1, C16.1, C17.1, C18.1, C19.2, C20.1, C22.1, C23.1, C24.1, C27.2, C28.1, C29.1, C30.2, C31.2, C32.2, D3.2, J1.1, J2.1, J3.1, J4.1, J5.1, JDC1.2, JDC1.3, Q3.2, Q4.2, Q5.2, Q6.2, R3.1, R6.1, R7.2, R31.1, R34.1, R39.1, R40.1, U1.3, U2.3, U3.2, U4.8, U5.10, U6.6, U6.7, U11.2, U12.2
LED0: LED6.1, U6.1
LED1: LED5.1, U6.2
LED2: R23.2, U6.3
LED3: R25.1, U6.4
NetC1_1: C1.1, L1.1, U1.2
NetC1_2: C1.2, U1.4
NetC4_1: C4.1, R2.1, R3.2, U1.6
NetC8_1: C8.1, L2.1, U2.2
NetC8_2: C8.2, U2.4
NetC11_1: C11.1, R5.1, R6.2, U2.6
NetC17_2: C17.2, FB1.1, SW5.2
NetC21_1: C21.1, U5.6
NetC21_2: C21.2, U5.4
NetD2_2: D2.2, R7.1
NetD3_1: D3.1, R14.2
NetD4_1: D4.1, R27.2
NetD5_2: D5.2, Q3.3, R27.1, U7.2
NetD6_1: D6.1, R32.2
NetD7_2: D7.2, Q4.3, R32.1, U8.2
NetD8_1: D8.1, R35.2
NetD9_1: D9.1, R36.2
NetD10_2: D10.2, Q6.3, R35.1, U9.2
NetD11_2: D11.2, Q5.3, R36.1, U10.2
NetJP1_1: JP1.1, U5.12
NetLED1_1: LED1.1, R20.2
NetLED1_2: LED1.2, U11.3
NetLED2_1: LED2.1, LED3.1, LED4.1, U12.3
NetLED2_2: LED2.2, R15.2
NetLED3_2: LED3.2, R16.2
NetLED4_2: LED4.2, R17.2
NetLED5_2: LED5.2, R18.2
NetLED6_2: LED6.2, R19.2
NetQ3_1: Q3.1, R30.2, R31.2
NetQ4_1: Q4.1, R33.2, R34.2
NetQ5_1: Q5.1, R37.2, R39.2
NetQ6_1: Q6.1, R38.2, R40.2
NetR1_1: R1.1, U1.5
NetR4_1: R4.1, U2.5
NetR8_2: R8.2, TP1.1, U4.13
NetR23_1: R23.1, U12.1
NetR25_2: R25.2, U11.1
NetR30_1: R30.1, U4.4
NetR33_1: R33.1, U4.7
NetR37_1: R37.1, U4.6
NetR38_1: R38.1, U4.5
NetTP3_1: TP3.1, U5.8
PUMP1_IN: C23.2, R12.1, SW1.1, SW1.2, U4.11
PUMP2_IN: C24.2, R13.1, SW2.1, SW2.2, U4.12
RES: R11.2, TP2.1, U5.9
SCL: J1.4, J2.4, J3.4, J4.4, J5.4, R10.2, R22.2, U4.14, U5.3, U6.8
SDA: J1.3, J2.3, J3.3, J4.3, J5.3, R9.2, R21.2, U4.15, U5.2, U6.9
VALVE1_IN: C29.2, R29.1, SW4.1, SW4.2, U4.9
VALVE2_IN: C28.2, R28.1, SW3.1, SW3.2, U4.10
VIN: C2.2, C3.2, C9.2, C10.2, D1.2, R1.2, R4.2, R20.1, U1.1, U2.1

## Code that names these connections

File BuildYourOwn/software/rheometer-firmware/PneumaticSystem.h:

// SPDX-License-Identifier: MIT
// Copyright (c) 2026 Charlie Vuong -- see LICENSE
#ifndef PNEUMATIC_SYSTEM_H
#define PNEUMATIC_SYSTEM_H

#include <Arduino.h>
#include <Wire.h>
#include <SparkFun_MicroPressure.h>
#include <Adafruit_seesaw.h>   // Adafruit ATtiny1616 Breakout with seesaw -- Library Manager: "Adafruit seesaw Library"
#include "OSCHandler.h"

// ---- Build flags ------------------------------------------------------------
#define SERIAL_STREAM 1        // USB serial bench stream; set 0 to disable

// ---- Qwiic bus (I2C, shared/daisy-chained): Button + MicroPressure + this
// ATtiny1616 seesaw board all hang off the ESP32's single Qwiic connector. -----
#define MPRLS_I2C_ADDR   0x18
#define SEESAW_I2C_ADDR  0x49   // Adafruit seesaw factory default (no address jumpers needed --
                                 // doesn't collide with MPRLS 0x18 or Qwiic Button 0x6F)

// ---- Pump/valve control -- routed through the ATtiny1616 seesaw board ------
// Earlier builds sourced PUMP1_EN/PUMP2_EN from ESP32 pins 32/33 (LEDC PWM)
// and VALVE2_EN from pin 14. Here the Adafruit ATtiny1616 breakout (seesaw
// firmware) sits between the ESP32 and the two L298N drivers, carrying those
// three connected signals -- and unlike a plain digital
// I2C GPIO expander (no PWM), seesaw exposes REAL 8-bit PWM over I2C
// (Adafruit_seesaw::analogWrite), so pump drive stays fully proportional.
// RheoSystem's REP phase machine, config percentages, and ramp logic are
// therefore UNCHANGED; only the low-level primitives below differ.
#define SS_PUMP1_EN   0   // was ESP32 pin 32 (vacuum pump, L298N #1 ENA) -- seesaw PWM pin
#define SS_PUMP2_EN   1   // was ESP32 pin 33 (pressure pump, L298N #1 ENB) -- seesaw PWM pin
#define SS_VALVE1_EN  4   // reserved for future VALVE1; physically NC in this single-valve build
#define SS_VALVE2_EN  5   // was ESP32 pin 14 (the only valve driven -- flip selector) -- plain GPIO

// ---- Optional bench extras (native ESP32 pins; unaffected by the seesaw move)
#define PIN_SW1   -1     // optional external REP button to GND; -1 = none
#define PIN_LED1  -1     // optional external status LED; -1 = none

#define PWM_FREQ_HZ     1000   // set via Adafruit_seesaw::setPWMFreq
#define VALVE_SETTLE_MS 15     // valve-flip guard before pump drive

// ---- Pressure sampling ------------------------------------------------------
#define DEFAULT_RATE 10        // ms between samples
#define MIN_RATE     10
#define MAX_RATE     1000

extern SparkFun_MicroPressure mpr;
extern Adafruit_seesaw ss;   // ATtiny1616 seesaw driving PUMP1/PUMP2/VALVE2; VALVE1 pin is reserved

enum PumpChannel { PUMP_1 = 1, PUMP_2 = 2 };

// ---- Pump / valve / sensor primitives ---------------------------------------
inline void pumpSetPct(PumpChannel c, int pct) {
  pct = constrain(pct, 0, 100);
  uint8_t duty = (uint8_t)((pct * 255) / 100);
  ss.analogWrite(c == PUMP_1 ? SS_PUMP1_EN : SS_PUMP2_EN, duty);
}
inline void pumpSet(PumpChannel c, bool on) { pumpSetPct(c, on ? 100 : 0); }
inline void pumpsOff()         { pumpSet(PUMP_1, false); pumpSet(PUMP_2, false); }
inline void ledExt(bool on)    { if (PIN_LED1 >= 0) digitalWrite(PIN_LED1, on ? HIGH : LOW); }
inline bool sw1Pressed()       { return PIN_SW1 >= 0 && digitalRead(PIN_SW1) == LOW; }
inline float readPressure()    { return mpr.readPressure(PA); }
inline void valveSuck() { ss.digitalWrite(SS_VALVE2_EN, LOW);  }
inline void valveBlow() { ss.digitalWrite(SS_VALVE2_EN, HIGH); }

bool halBegin();
void sendApiEntry(const char* entry);  // notifies one /rheo/api reply line over BLE TX

// ============================================================================
// PneumaticSystem — pump/valve/sensor control + /pump/* /valve/* /system/* OSC
// ============================================================================
class PneumaticSystem {
public:
    bool          manualBlowing = false;
    bool          latchedSuck   = false;
    bool          testStreaming = false;
    unsigned long testStart     = 0;
    float         pressure      = 0.0f;
    int           rate          = DEFAULT_RATE;

    // Explicit power (0-100); subclasses may override to supply a default.
    virtual void blow(int power);
    virtual void suck(int power);      // latches until stopSuck
    void         stopBlow();
    void         stopSuck();
    void         cancelSuck();
    void         toggleSuck();         // calls suck(-1) so subclass default applies

    void off();        // /pump/off    — pumps off, valve unchanged
    void purge();      // /pump/purge  — clear line with pressure, then rest
    void valveOn();    // /valve/on    — energize valve (pressure path, no pump)
    void valveOff();   // /valve/off   — de-energize valve (vacuum path, no pump)
    void systemOff();  // /system/off  — emergency stop: pumps off, valve park, reset state

    // Pressure sensing
    virtual unsigned long sessionStart() const { return 0; }
    void sampleAir();     // read pressure, send /rheo/sense/air, delay(rate)
    void sampleTest();    // bench stream: #S,<ms>,<Pa> then delay(rate)

    // Bench pump-test
    virtual bool isActive() const;
    void startPumpTest(PumpChannel ch, int pct);
    void stopPumpTest();

    virtual void setup();
    virtual void loop();

    virtual void printApi();
    virtual bool routeOSC(OSCMessage& msg, char* buffer);
};

#endif // PNEUMATIC_SYSTEM_H

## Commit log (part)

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2026-06-04 Update Final
